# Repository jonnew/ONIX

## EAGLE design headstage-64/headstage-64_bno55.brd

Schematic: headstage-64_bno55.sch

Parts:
C1: 0.1uF; 0201T; PARTNP CL03A104KA3NNNC
C2, C3, C6, C7, C19, C31, C35, C37, C79: 0.1uF; 0201T; PARTNO C0603X5R1C104K030BC
C4, C39, C41, C43, C57, C65, C74: 1uF; 0402T; PARTNO CL05A105KO5NNNC
C5, C9, C10: 0.1uF; 0201T; PARTNO CL03A104KA3NNNC
C8: 4.7uF; 0402T; PARTNO CL05A475MO5NUNC
C11, C15, C16, C22, C23, C47, C53, C61, C68, C73: 10nF; 0201T
C12, C14, C17, C21, C24, C34, C50, C76, C78: 0.1uF; 0201T
C13, C18: 4.7uF; 0402T; PARTNO GRM155R61A475MEAAD
C20, C32, C36, C38, C51: 1uF; 0201T; PARTNO CL03A105MP3ZSNH
C25: 22uF; 0402T; PARTNO CL05A226MQ5QUNC
C29: 0.1uF; 0201T; PARTNO C1005X7R1H104K050BB
C30: 47nF; 0201T; PARTNO C1005X7R1H473K050BB
C33: 10nF; 0201T; PARTNO GRM033R71E103KE14D
C40, C42, C56, C58: 10uF; 0402T; PARTNO CL05A106MQ5NUNC
C44, C66: 0.22uF; 0402T; PARTNO UMK105BJ224KV-F
C45: 2.2nF; 0201T
C46, C52, C60, C67: 4.7nF; 0201T
C48, C54, C62, C69: 22nF; 0201T
C49, C63: 47nF; 0201T
C55, C64, C70: 0.47uF; 0201T; PARTNO GRM033R60J474KE90D
C59: 10pF; 0201T
C71: 2.2uF; 0402T; PARTNO CL05A105KO5NNNC
C72: 4.7uF; 0402T; PARTNO CL05A105KO5NNNC
C75: 22uF; 0402T; PARTNO CL05A226MQ6ZUN8
C77: 6.8nF; 0201T; PARTNO CL03B103KP3NNNC
C80, C81: 22pF, NP0 2%; 0402T
D1, D2, D3: SESD0402X1UN-0020-090; 0402T-DFN
D4, D5, D6, D8: VEMD1160X01; 0805PT
D7: XZVGR155W; LED-0201T
D9: VSKY05401006; CLP1006-2L
J1, J3, J6: COAX_XFL; X_FL_R_SMT_1(02)
J2, J4, J7: PINHD-1X4HEADSTAGE64-DAUGHTER-CARD-CASTELLATED; HEADSTAGE64-DAUGHER-CARD-CASTELLATED
J5: PINHD-1X4HEADSTAGE64_DAUGHTER-CARD; HEADSTAGE-64-DAUGHTER-CARD
J8: DF40C-70DP-0.4V(51); DF40-70HEAD-LESS-SILK
J9: PINHD-1X5_HALF_CONNETOR; DF40-10HEAD_HALF
L1, L3, L5: CIG21L4R7MNE; 0805T
L2: BLM18KG601SN1D; 0603T
L4: CBC3225T101MR; 1210T
L6, L7, L8, L10: BLM15PX601SN1D; 0402T; PARTNO BLM15PX601SN1D
L9, L11: MLZ2012M100WT000; 0805T
L12: LQM21PN1R0NGRD; 0805T
R1, R4, R5, R6, R7, R8, R14, R16, R17, R18, R19: 10k, 0.1%; 0201T
R2: 1k, 0.1%; 0201T
R3, R9, R10, R20, R21, R40: 1k; 0201T
R11: 9k, 0.1%; 0201T
R12, R30, R32, R33, R44: 100; 0201T
R13: 2.86k; 0201T
R15: 590; 0201T
R22, R23, R27, R31, R35, R36, R37, R46, R49, R50, R51, R52, R53, R54, R55: 10k; 0201T
R24, R26, R34, R39: 15k; 0201T
R25: 49.9; 0201T
R28: 0; 0201T
R29: 100k; 0201T
R38: 2k; 0201T
R41, R48, R56, R57: 4.7k; 0201T
R42, R47: 1M; 0201T
R43: 90.9k; 0201T
R45: 83.3k; 0201T
TP1, TP2, TP5, TP6: VCC; TP07R
TP3, TP4: TPTP09R; TP09R
TP7, TP8, TP9, TP10, TP11, TP12, TP13: TPTP06R; TP06R
TP14: gnd; TP06R
TP15: VCC; TP06R
TP16, TP17: TPTP07R; TP07R
U1: ADA4062-4ACPZ-R7; CP_16_27-L
U2: AD5681RBCPZ-1RL7; CP_8_10-L
U3: CAT4016_QFN; QFN24-4X4; PARTNO CAT4016HV6-GT2
U4: TPL0501_UQFN; UQFN; PARTNO TPL0501-100RSER
U5: DG509B; MQFN16-1.8X2.6
U6, U9, U11, U12: TS4231; WLCSP3X3
U8: RHD2064_BGA; BGA104_0.5MM
U10: DS90UB913A_WQFN; WQFN32-5X5
U13, U15: TLV70733; X2SON
U14: 10M08DC; VBGA81-4X4
U16: LT3463; DFN103X3
U17: TLV70725; X2SON
U18: TPS62621; XBGA6_1.2X0.8
U19: ASCO-50.000MHZ-EK-T3; ASCO
U20: TLV70712; X2SON
U21: BNO055; LGA-28-3.8X5.2
Y2: ECS-.327-12.5-1210-TR; ECX-1210

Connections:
!IMU_BL: R54.2, TP16.TP, U21.4 (!BOOT_LOAD)
!IMU_RESET: R55.1, U21.11 (!RESET)
$N324: C52.1, C53.1, C54.1, C55.1, C56.1, L10.2, U14.A8 (VCCD_PLL2)
+1V2: C45.1, C46.1, C47.1, C48.1, C49.1, C50.1, C51.1, C75.1, L10.1, U14.B2 (VCC), U14.B9 (VCC), U14.H2 (VCC), U14.H8 (VCC), U20.1 (OUT)
+1V8: C14.1, C15.1, C16.1, C17.1, C18.1, C72.1, L6.1, L8.1, L12.1, R27.1, U10.11 (VDDT), U10.28 (VDDD), U18.C1 (FB)
+2V5: C58.1, C67.1, C68.1, C69.1, C70.1, C74.1, U14.B1 (VCCA3), U14.B8 (VCCA2), U14.J1 (VCCA1), U14.J9 (VCCA4), U17.1 (OUT), U20.3 (EN), U20.4 (IN)
+3V3: C3.1, C6.1, C19.1, C21.1, C22.1, C31.1, C35.1, C37.1, C42.1, C60.1, C61.1, C62.1, C63.1, C64.1, C73.1, C76.1, C77.1, C78.1, R22.1, R31.1, R35.1, R36.1, R37.1, R38.1, R41.1, R48.1, R49.1, R50.1, R51.1, R52.1, R54.1, R55.2, R56.2, R57.2, TP14.TP, U2.2 (VLOGIC), U4.7 (VDD), U6.C3 (DVDD), U9.C3 (DVDD), U10.25 (VDDIO), U11.C3 (DVDD), U12.C3 (DVDD), U14.D5 (VCCIO8), U14.E4 (VCCIO1_2), U14.E6 (VCCIO5_6), U14.F5 (VCCIO3), U15.1 (OUT), U19.1 (EN), U19.4 (VCC), U21.3 (VDD), U21.28 (VDDIO)
+3V3_AN: C34.2, C40.1, J9.4 (5), U8.M15 (VDD), U8.M16 (LVDS_EN), U8.N2 (VDD), U8.N15 (VDD), U13.1 (OUT)
+15V0: C1.1, C9.1, C44.1, R42.2, U1.3 (V+), U5.12 (V+), U16.1 (VOUT1)
-15V0: C5.1, C10.1, C59.2, C66.1, D9.A, R47.1, U1.10 (V-), U1.PAD (V-), U5.1 (V-)
AGND: C33.2, C34.1, C39.2, C40.2, J8.70, J8.M1, J8.M2, J8.M4, J9.M1 (1), J9.M2 (6), L7.2, R28.1, TP1.TP, U8.M2 (VESD), U8.M17 (GND), U8.N1 (GND), U8.N6 (GND), U13.2 (GND), U13.PAD (GND)
AUXIN2: J9.2 (3), TP6.TP, U8.N4 (AUXIN2)
AUXIN3: J9.1 (2), TP5.TP, U8.N3 (AUXIN1)
CONFIG_SEL: R53.1, U14.C6 (CONFIG_SEL/C6)
CONF_DONE: R52.2, U14.A2 (DIFFIO_RX_T24N/CONF_DONE/A2)
DAC_CS: U2.5 (!SYNC), U14.A5 (DIFFIO_RX_T18N/A5)
DATA1: U6.C1 (D/CFGDATA), U14.C7 (DIFFIO_RX_R33P/PLL_R_CLKOUTP/C7)
DATA2: U9.C1 (D/CFGDATA), U14.C3 (DIFFIO_RX_T26N/C3)
DATA3: U11.C1 (D/CFGDATA), U14.A7 (DIFFIO_RX_T16P/A7)
DATA4: U12.C1 (D/CFGDATA), U14.B6 (DIFFIO_RX_T16N/DEV_CLRN/B6)
DIN0: U10.19 (DIN0), U14.J6 (DIFFIO_TX_RX_B12P/J6)
DIN1: U10.20 (DIN1), U14.G6 (DIFFIO_TX_RX_B14N/G6)
DIN2: U10.21 (DIN2), U14.H7 (DIFFIO_TX_RX_B14P/H7)
DIN3: U10.22 (DIN3), U14.J7 (DIFFIO_TX_RX_B16N/J7)
DIN4: U10.23 (DIN4), U14.G8 (DIFFIO_RX_R7P/G8)
DIN5: U10.24 (DIN5), U14.G9 (DIFFIO_RX_R7N/G9)
DIN6: U10.26 (DIN6), U14.F7 (DIFFIO_RX_R1N/F7)
DIN7: U10.27 (DIN7), U14.E7 (DIFFIO_RX_R14N/CLK2N/E7)
DIN8: U10.29 (DIN8), U14.E8 (DIFFIO_RX_R14P/CLK2P/E8)
DIN9: U10.30 (DIN9), U14.C8 (DIFFIO_RX_R27P/C8)
DIN10: U10.31 (DIN10), U14.C5 (CRC_ERROR/C5)
DIN11: U10.32 (DIN11), U14.C4 (DIFFIO_RX_T26P/C4)
E0: J8.2, U8.K2 (IN0)
E1: J8.68, U8.J1 (IN1)
E2: J8.3, U8.J2 (IN2)
E3: J8.67, U8.H1 (IN3)
E4: J8.4, U8.H2 (IN4)
E5: J8.66, U8.G1 (IN5)
E6: J8.5, U8.G2 (IN6)
E7: J8.65, U8.F1 (IN7)
E8: J8.6, U8.F2 (IN8)
E9: J8.64, U8.E1 (IN9)
E10: J8.7, U8.E2 (IN10)
E11: J8.63, U8.D1 (IN11)
E12: J8.8, U8.D2 (IN12)
E13: J8.62, U8.C1 (IN13)
E14: J8.9, U8.C2 (IN14)
E15: J8.61, U8.B1 (IN15)
E16: J8.10, U8.A1 (IN16)
E17: J8.60, U8.B2 (IN17)
E18: J8.11, U8.A2 (IN18)
E19: J8.59, U8.B3 (IN19)
E20: J8.12, U8.A3 (IN20)
E21: J8.58, U8.B4 (IN21)
E22: J8.13, U8.A4 (IN22)
E23: J8.57, U8.B5 (IN23)
E24: J8.14, U8.A5 (IN24)
E25: J8.56, U8.B6 (IN25)
E26: J8.15, U8.A6 (IN26)
E27: J8.55, U8.B7 (IN27)
E28: J8.16, U8.A7 (IN28)
E29: J8.54, U8.B8 (IN29)
E30: J8.17, U8.A8 (IN30)
E31: J8.53, U8.B9 (IN31)
E32: J8.18, U8.A9 (IN32)
E33: J8.52, U8.A10 (IN33)
E34: J8.19, U8.B10 (IN34)
E35: J8.51, U8.A11 (IN35)
E36: J8.20, U8.B11 (IN36)
E37: J8.50, U8.A12 (IN37)
E38: J8.21, U8.B12 (IN38)
E39: J8.49, U8.A13 (IN39)
E40: J8.22, U8.B13 (IN40)
E41: J8.48, U8.A14 (IN41)
E42: J8.23, U8.B14 (IN42)
E43: J8.47, U8.A15 (IN43)
E44: J8.24, U8.B15 (IN44)
E45: J8.46, U8.A16 (IN45)
E46: J8.25, U8.B16 (IN46)
E47: J8.45, U8.A17 (IN47)
E48: J8.26, U8.B17 (IN48)
E49: J8.44, U8.C16 (IN49)
E50: J8.27, U8.C17 (IN50)
E51: J8.43, U8.D16 (IN51)
E52: J8.28, U8.D17 (IN52)
E53: J8.42, U8.E16 (IN53)
E54: J8.29, U8.E17 (IN54)
E55: J8.41, U8.F16 (IN55)
E56: J8.30, U8.F17 (IN56)
E57: J8.40, U8.G16 (IN57)
E58: J8.31, U8.G17 (IN58)
E59: J8.39, U8.H16 (IN59)
E60: J8.32, U8.H17 (IN60)
E61: J8.38, U8.J16 (IN61)
E62: J8.33, U8.J17 (IN62)
E63: J8.37, U8.K16 (IN63)
ENV1: U6.C2 (E/CFGCLK), U14.B5 (DIFFIO_RX_T19N/B5)
ENV2: U9.C2 (E/CFGCLK), U14.C2 (DIFFIO_RX_L1N/C2)
ENV3: U11.C2 (E/CFGCLK), U14.D9 (DIFFIO_RX_R16N/CLK3N/D9)
ENV4: U12.C2 (E/CFGCLK), U14.B7 (DIFFIO_RX_R33N/PLL_R_CLKOUTN/B7)
ESTIM_POW_EN: R46.1, U14.A6 (DIFFIO_RX_T18P/DEV_OEA6), U16.8 (!SHDN2), U16.9 (!SHDN1)
GND: C1.2, C2.2, C3.2, C4.2, C5.2, C6.2, C7.2, C8.2, C9.2, C10.2, C11.2, C12.2, C13.2, C14.2, C15.2, C16.2, C17.2, C18.2, C19.2, C20.2, C21.2, C22.2, C23.2, C24.2, C25.2, C31.2, C32.2, C35.2, C36.2, C37.2, C38.2, C41.2, C42.2, C43.2, C44.2, C45.2, C46.2, C47.2, C48.2, C49.2, C50.2, C51.2, C52.2, C53.2, C54.2, C55.2, C56.2, C57.2, C58.2, C60.2, C61.2, C62.2, C63.2, C64.2, C66.2, C67.2, C68.2, C69.2, C70.2, C71.2, C72.2, C73.2, C74.2, C75.2, C76.2, C77.2, C78.2, C79.1, C80.2, C81.2, J5.2, J5.4, L7.1, R19.1, R21.1, R23.2, R24.1, R25.1, R26.1, R29.2, R34.1, R39.1, R40.2, R43.1, R46.2, R53.2, TP3.TP, TP15.TP, U2.3 (GND), U2.PAD (GND), U3.1 (GND), U3.PAD (GND), U4.4 (GND), U4.8 (LA), U5.2 (X0), U5.13 (GND), U5.14 (B), U6.B2 (AVSS), U6.B3 (AVSS2), U9.B2 (AVSS), U9.B3 (AVSS2), U10.6 (ID), U10.7 (RES), U10.PAD (GND), U11.B2 (AVSS), U11.B3 (AVSS2), U12.B2 (AVSS), U12.B3 (AVSS2), U14.A1 (GND), U14.A9 (GND), U14.B4 (GND), U14.D1 (GND), U14.D7 (GND), U14.E5 (GND), U14.E9 (GND), U14.F4 (GND), U14.F6 (GND), U14.H1 (GND), U14.H5 (GND), U14.H9 (GND), U15.2 (GND), U15.PAD (GND), U16.PAD (GND), U17.2 (GND), U17.PAD (GND), U18.C2 (GND), U19.2 (GND), U20.2 (GND), U20.PAD (GND), U21.2 (GND), U21.5 (PS1), U21.6 (PS0), U21.15 (GNDIO), U21.16 (GNDIO), U21.17 (COM3/ADDR), U21.18 (COM2), U21.25 (GNDIO)
GND1: D2.A, J3.P$2 (2), J3.P$3 (2), J3.P$4 (2), J4.2, J4.4
GND2: D1.A, J1.P$2 (2), J1.P$3 (2), J1.P$4 (2), J2.2, J2.4
GND3: D3.A, J6.P$2 (2), J6.P$3 (2), J6.P$4 (2), J7.2, J7.4
GPIO0: J9.3 (4), TP4.TP, U10.15 (GPIO0), U14.A3
GPIO1: U10.16 (GPIO1), U14.H6 (DIFFIO_TX_RX_B12N/H6)
HSYNC: U10.1 (HSYNC), U14.F2 (DIFFIO_RX_L18P/CLK0P/F2)
IMU_BL_IND: TP17.TP, U21.10 (BL_IND)
IMU_INT: U21.14 (INT)
IMU_SCL: R56.1, U14.E3, U21.19 (COM1/SCL/RX)
IMU_SDA: R57.1, U14.F9 (DIFFIO_RX_R10N/F9), U21.20 (COM0/SDA/TX)
ISTIM: J8.1, U5.6 (X), U5.10 (Y1)
ISTIM_MONO: R14.1, R19.2, U8.N5 (AUXIN3)
ISTIM_PRE: R12.1, U1.9 (+IN), U5.7 (Y)
JTAGEN: R35.2, U14.D2 (JTAGEN/D2)
LED-1: J8.34, U3.5 (LED1), U3.6 (LED2), U3.7 (LED3), U3.8 (LED4), U3.9 (LED5), U3.10 (LED6), U3.11 (LED7), U3.12 (LED8)
LED-2: J8.35, U3.13 (LED9), U3.14 (LED10), U3.15 (LED11), U3.16 (LED12), U3.17 (LED13), U3.18 (LED14), U3.19 (LED15), U3.20 (LED16)
LED_BLANK: R49.2, U3.21 (BLANK), U14.C9 (DIFFIO_RX_R27N/C9)
LED_LATCH: U3.4 (LATCH), U14.J8 (DIFFIO_TX_RX_B16P/J8)
MIDFILT: J5.1, L4.1, R10.1
MOSI: U2.6 (DIN), U3.2 (SIN), U4.2 (DIN), U14.A4 (DIFFIO_RX_T19P/A4)
unnamed: R15.2, U4.6 (WA)
unnamed: C65.1, L11.1, U16.4 (SW2)
unnamed: C59.1, R45.1, R47.2, U16.6 (FB2)
unnamed: D4.C, U6.A3 (IIN-)
unnamed: D4.A, U6.A2 (IIN+)
unnamed: R24.2, U6.B1 (RBIAS)
unnamed: C20.1, U6.A1 (AVDD)
unnamed: L9.1, U16.2 (SW1)
unnamed: D5.C, U9.A3 (IIN-)
unnamed: D5.A, U9.A2 (IIN+)
unnamed: R26.2, U9.B1 (RBIAS)
unnamed: C32.1, U9.A1 (AVDD)
unnamed: C7.1, C8.1, L2.1, L4.2, R10.2
unnamed: R15.1, U3.23 (RSET)
unnamed: D6.C, U11.A3 (IIN-)
unnamed: D6.A, U11.A2 (IIN+)
unnamed: R34.2, U11.B1 (RBIAS)
unnamed: C36.1, U11.A1 (AVDD)
unnamed: C65.2, D9.C, U16.5 (D2)
unnamed: R1.2, R2.2, R12.2, U1.4 (+IN)
unnamed: C81.1, U21.26 (XOUT32), Y2.P$2 (2)
unnamed: C80.1, U21.27 (XIN32), Y2.P$1 (1)
unnamed: R21.2, U5.11 (Y0)
unnamed: R42.1, R43.2, U16.10 (FB1)
unnamed: J4.1, L3.2, R9.2
unnamed: D8.C, TP7.TP, U12.A3 (IIN-)
unnamed: R45.2, U16.7 (VREF)
unnamed: C29.2, U10.13 (DOUT+)
unnamed: D7.2 (A), R38.2
unnamed: R31.2, U10.9 (PDB)
unnamed: C30.2, U10.12 (DOUT-)
unnamed: C30.1, R25.2
unnamed: R27.2, R29.1, U10.8 (MODE)
unnamed: C11.1, C12.1, C13.1, L6.2, U10.10 (VDDPLL)
unnamed: C23.1, C24.1, C25.1, L8.2, U10.14 (VDDCML)
unnamed: C33.1, U8.N17 (ADC_REF)
unnamed: U14.D8 (DIFFIO_RX_R16P/CLK3P/D8), U19.3 (OUT)
unnamed: D8.A, TP8.TP, U12.A2 (IIN+)
unnamed: TP2.TP, U8.N16 (AUXOUT)
unnamed: R39.2, U12.B1 (RBIAS)
unnamed: C38.1, U12.A1 (AVDD)
unnamed: R22.2, U5.16 (EN)
unnamed: R50.2, U14.D6 (NCONFIG/D6)
unnamed: L12.2, U18.B1 (SW)
unnamed: J2.1, L1.2, R3.2
unnamed: J7.1, L5.2, R20.2
unnamed: R1.1, R4.2, U1.2 (+IN)
unnamed: R5.2, R11.1, U1.1 (-IN)
unnamed: R2.1, R11.2, U1.15 (OUT)
unnamed: R16.1, R17.2, U1.6 (OUT)
unnamed: R13.1, R16.2, U1.5 (-IN)
unnamed: R8.1, R13.2, U1.8 (-IN)
unnamed: R6.2, R8.2, U1.7 (OUT)
unnamed: R7.1, R14.2, U1.14 (OUT)
unnamed: R6.1, R7.2, U1.12 (-IN)
unnamed: R17.1, R18.2, U1.11 (+IN)
unnamed: C79.2, U21.9 (CAP)
NSTATUS: R51.2, U14.B3 (DIFFIO_RX_T24P/NSTATUS/B3)
PCLK: U10.3 (PCLK1), U14.G2 (DIFFIO_RX_L20N/CLK1N/G2)
POT_CS: U4.3 (!CS), U14.G7 (DIFFIO_RX_R1P/G7)
REF: J8.69, R28.2, U8.M1 (REF_ELEC)
RHD_CLK_N: R32.1, U8.N9 (SCLK-), U14.G5 (DIFFIO_TX_RX_B3P/G5)
RHD_CLK_P: R32.2, U8.N10 (SCLK+), U14.G4 (DIFFIO_TX_RX_B3N/G4)
RHD_CS_N: R30.1, U8.N7 (!CS!-), U14.J2 (DIFFIO_TX_RX_B1P/J2)
RHD_CS_P: R30.2, U8.N8 (!CS!+), U14.H3 (DIFFIO_TX_RX_B1N/H3)
RHD_MISO_N: R44.1, U8.N13 (MISO-), U14.J5 (DIFFIO_TX_RX_B9P/J5)
RHD_MISO_P: R44.2, U8.N14 (MISO+), U14.J4 (DIFFIO_TX_RX_B9N/J4)
RHD_MOSI_N: R33.1, U8.N11 (MOSI-), U14.H4 (DIFFIO_TX_RX_B5P/H4)
RHD_MOSI_P: R33.2, U8.N12 (MOSI+), U14.J3 (DIFFIO_TX_RX_B5N/J3)
SCL: R41.2, U10.4 (SCL), U14.G3 (DIFFIO_RX_L27P/G3)
SCLK: U2.4 (SCLK), U3.3 (CLK), U4.5 (SCLK), U14.F3 (DIFFIO_RX_L27N/F3)
SDA: R48.2, U10.5 (SDA), U14.F8 (DIFFIO_RX_R10P/F8)
SIGOUT: C29.1, J5.3
STATUS: D7.1 (C), U14.C1 (DIFFIO_RX_L1P/C1)
STIM_NULL: R23.1, U5.15 (A), U14.F1 (DIFFIO_RX_L18N/CLK0N/F1)
TCK: R40.1, TP11.TP, U14.D4 (DIFFIO_RX_L11P/TCK/D4)
TDI: R37.2, TP12.TP, U14.E1 (DIFFIO_RX_L12N/TDI/E1)
TDO: TP13.TP, U14.E2 (DIFFIO_RX_L12P/TDO/E2)
TMS: R36.2, TP10.TP, U14.D3 (DIFFIO_RX_L11N/TMS/D3)
VCOAX: C2.1, C4.1, C39.1, C41.1, C43.1, C57.1, C71.1, J8.36, J8.M3, L2.2, L9.2, L11.2, TP9.TP, U2.1 (AVDD), U3.24 (VDD), U13.3 (EN), U13.4 (IN), U15.3 (EN), U15.4 (IN), U16.3 (VIN), U17.3 (EN), U17.4 (IN), U18.A1 (MODE), U18.A2 (VIN), U18.B2 (EN)
VDAC: R4.1, U2.8 (VOUT)
VREF_2V5: R5.1, R18.1, U2.7 (VREF)
VSYNC: U10.2 (VSYNC), U14.G1 (DIFFIO_RX_L20P/CLK1P/G1)
_SIGOUT: D2.C, J3.P$1 (1), J4.3, L3.1, R9.1
_SIGOUT1: D1.C, J1.P$1 (1), J2.3, L1.1, R3.1
_SIGOUT2: D3.C, J6.P$1 (1), J7.3, L5.1, R20.1

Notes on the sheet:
NB: Inductors pass 250mA DC max before they are used to generate a flyback voltage. Because we are dealing with a very low current application, we can probably get away with inductors that saturate below 250 mA so long as they are capable of handling the current. The MLZ2012M100WT000 saturates at 2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
NB: VCoax must NOT exceed 5.5V
Programming interface
INPUT
ESTIM
OPTOSTIM
SERIALIZER
FPGA
ADC
TRACKING
POWER
NB: Because we are suing a 3.3V IO voltage for bank 3, the LVDS produced here is technically out of spec. The lines sit at 1.6V and swing about 600 mV. This is a result of using 3.3V supply on an FPGA that nominally requires a 2.5 rail to get LVDS to its standard 1.2V common mode voltage with 400 m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
DNP
NB: CLK3 drives PLL2
NB: IO daughter boards. Multiple allows them to be replaced if coax connector gets worn out.
NB: ISTIM = (VDAC - 2.5)/1000. e.g. VDAC = 2.5 -> ISTIM = 0 VDAC = 5.0 -> ISTIM = 2.5 mA VDAC = 0.0 -> ISTIM = -2.5mA and Imeas = 400 * ISTIM + 1.25V e.g. ISTIM = 0 -> IMEAS = 1.25V ISTIM = 2.5mA -> IMEAS = 2.25V ISTIM = -2.5mA -> IMEAS = 0.25V
I2C Selected
NB To get the best performance out of BNO055, it is recommended to use the external 32.768 kHz crystal.

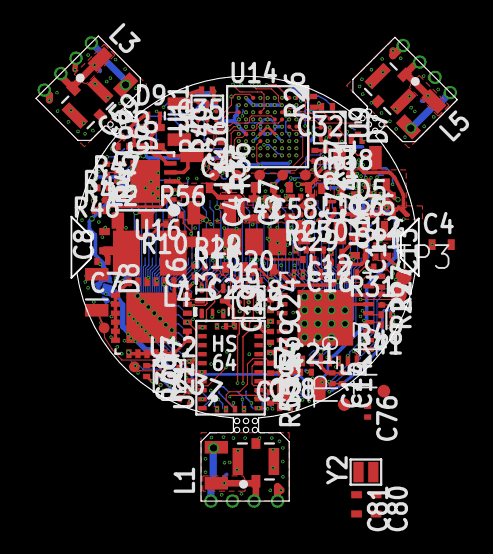
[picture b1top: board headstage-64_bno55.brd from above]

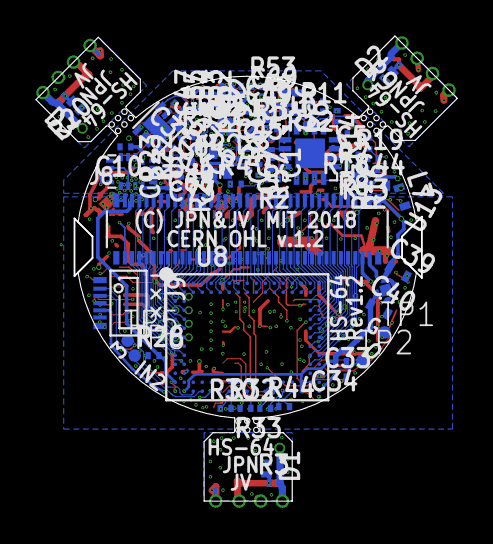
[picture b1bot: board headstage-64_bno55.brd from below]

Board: 8 copper layers, 23.4 x 25.8 mm, 203 parts (82 on the bottom side), 207 nets.

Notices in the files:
headstage-64/headstage-64_bno55.brd:
CERN OHL v.1.2
headstage-64/headstage-64_bno55.sch:
LICENSE: CERN OHL v1.2
headstage-neuropix/headstage-neuropix_no-test-fixtures.brd:
CERN OHL v1.2 JPN '19
headstage/headstage.brd:
CC BY-SA-NC-4.0
headstage/headstage.sch:
LICENSE: (c) Jon Newman CC-BY-SA-NC 4.0
